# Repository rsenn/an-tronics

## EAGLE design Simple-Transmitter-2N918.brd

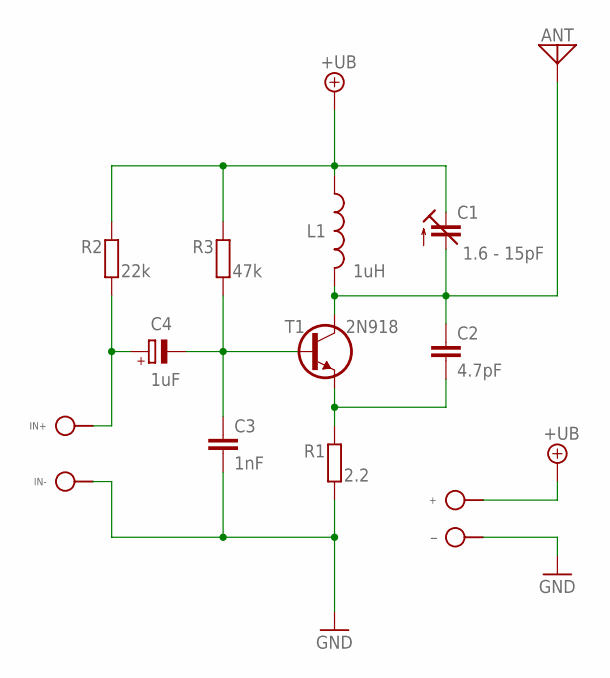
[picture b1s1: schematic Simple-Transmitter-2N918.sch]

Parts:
+: SPAD
ANT: ANT; SPAD
C1: 1.6 - 15pF; TRIM-2222-808
C2: 4.7pF; C025-020X036
C3: 1nF; C025-020X036
C4: 1uF; E2,5-3
IN+: SPAD
IN-: SPAD
L1: 1uH; L-04/7
R1: 2.2; 0202V
R2: 22k; 0202/5
R3: 47k; 0202/5
T1: 2N918; TO-72
̶̶: SPAD

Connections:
+UB: +.1, C1.3 (A), L1.1, R2.2, R3.2
GND: C3.2, IN-.1, R1.1, ̶̶.1
IN+: C4.+, IN+.1, R2.1
unnamed: ANT.1, C1.2 (E), C2.1, L1.2, T1.3 (C)
unnamed: C2.2, R1.2, T1.1 (E), T1.4 (E)
unnamed: C3.1, C4.-, R3.1, T1.2 (B)

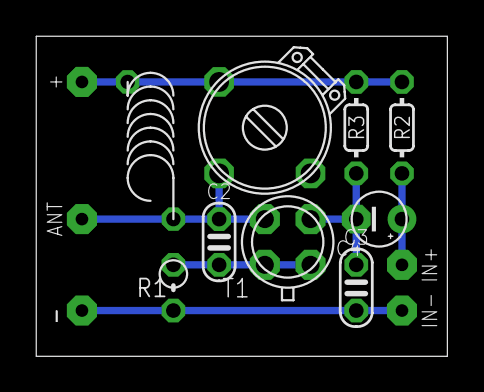
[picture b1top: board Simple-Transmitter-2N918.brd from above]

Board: 2 copper layers, 22.8 x 17.8 mm, 14 parts (0 on the bottom side), 6 nets.

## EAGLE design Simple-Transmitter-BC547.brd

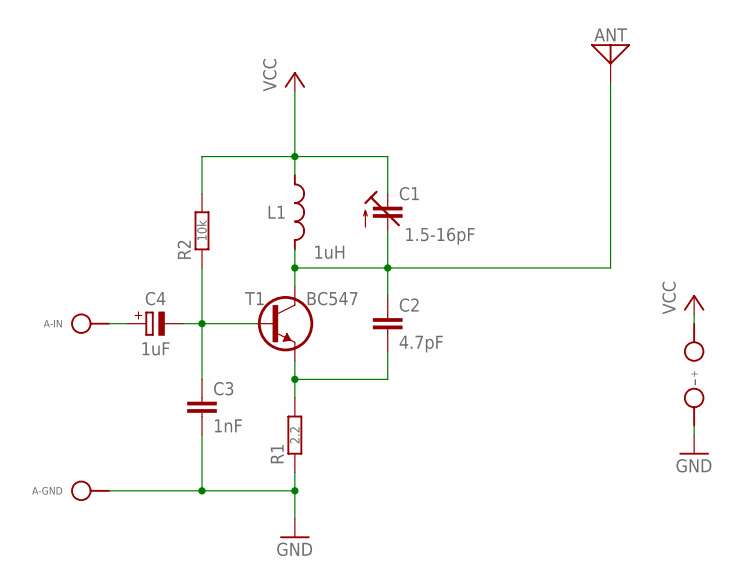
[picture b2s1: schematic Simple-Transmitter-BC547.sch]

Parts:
+: SPAD
A-GND: SPAD
A-IN: SPAD
ANT: ANT; SPAD
C1: 1.5-16pF; TRIM808-45
C2: 4.7pF; C050-020X036-M
C3: 1nF; C050-020X036
C4: 1uF; E2,5-3
L1: 1uH; L-04/7
R1: 2.2; 0202V
R2: 10k; 0202/5-V
T1: BC547; TO92-CBE
̶̶: SPAD

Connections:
AIN: A-IN.1, C4.+
GND: A-GND.1, C3.2, R1.1, ̶̶.1
unnamed: ANT.1, C1.2 (E), C2.1, L1.2, T1.C
unnamed: C2.2, R1.2, T1.E
unnamed: C3.1, C4.-, R2.1, T1.B
VCC: +.1, C1.3 (A), L1.1, R2.2

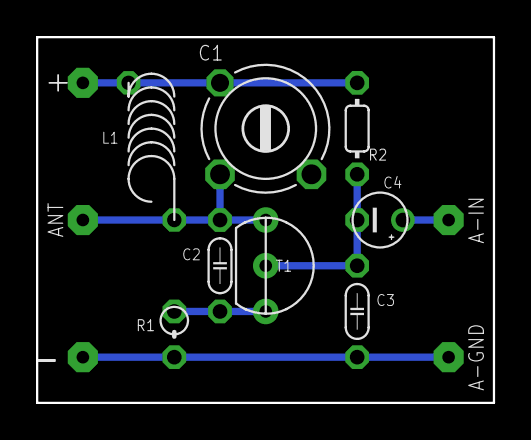
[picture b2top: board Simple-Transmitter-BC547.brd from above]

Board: 2 copper layers, 25.4 x 20.3 mm, 13 parts (0 on the bottom side), 6 nets.

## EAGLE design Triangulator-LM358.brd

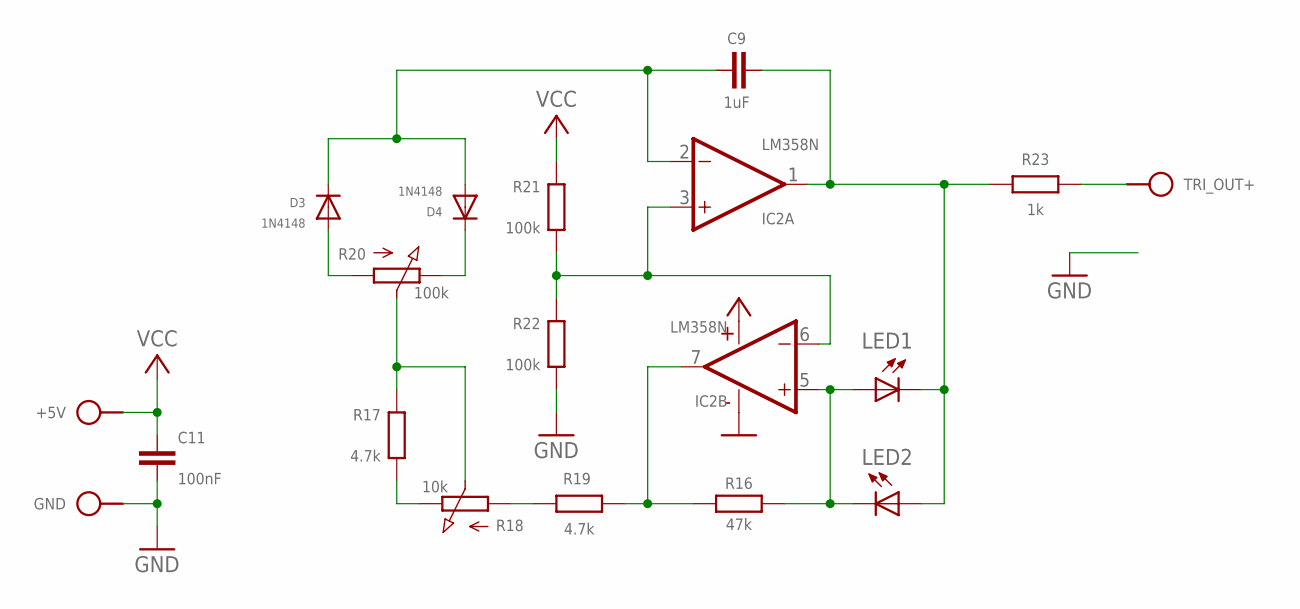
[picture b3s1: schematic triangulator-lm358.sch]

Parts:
+5V: VCC; SPAD
C9: 1uF; C050-020X036/V
C11: 100nF; C050-020X036
D3, D4: 1N4148; DO34-5V
GND: GND; SPAD
IC2: LM358N; DIL08
LED1, LED2: LED3MM
R16: 47k; 0202/7-V
R17: 4.7k; 0202/7
R18: 10k; POT
R19: 4.7k; 0202/7-V
R20: 100k; POT
R21, R22: 100k; 0202/7-V
R23: 1k; 0202/5
TRI_OUT+: TRIANGLE; SPAD

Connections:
GND: C11.2, GND.1, IC2.4 (V-), R22.1
unnamed: IC2.7 (OUT), R16.2, R19.1
unnamed: IC2.5 (+IN), LED1.A, LED2.K (C), R16.1
unnamed: D3.A, R20.1 (A)
unnamed: D4.C, R20.3 (E)
unnamed: R17.2, R18.2 (S), R20.2 (S)
unnamed: R17.1, R18.3 (E)
unnamed: C9.1, D3.C, D4.A, IC2.2 (-IN)
unnamed: R18.1 (A), R19.2
unnamed: C9.2, IC2.1 (OUT), LED1.K (C), LED2.A, R23.2
unnamed: R23.1, TRI_OUT+.1
unnamed: IC2.3 (+IN), IC2.6 (-IN), R21.1, R22.2
VCC: +5V.1, C11.1, IC2.8 (V+), R21.2

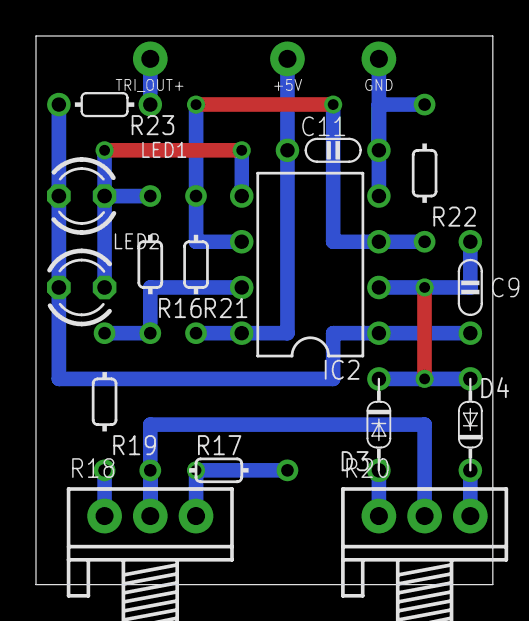
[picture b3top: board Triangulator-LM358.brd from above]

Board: 2 copper layers, 25.4 x 30.5 mm, 18 parts (0 on the bottom side), 13 nets.

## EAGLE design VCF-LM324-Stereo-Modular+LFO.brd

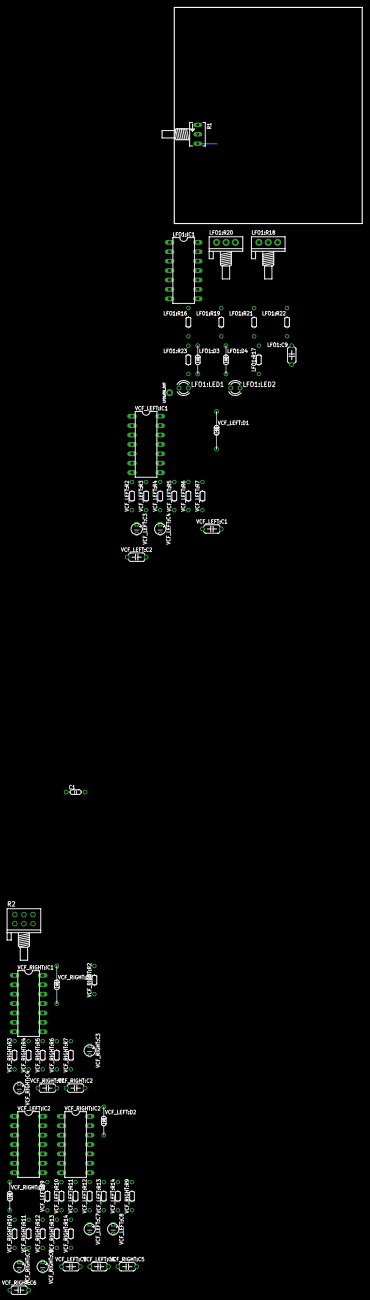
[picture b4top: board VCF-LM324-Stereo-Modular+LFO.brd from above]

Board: 2 copper layers, 50.8 x 58.4 mm, 66 parts (0 on the bottom side), 36 nets.

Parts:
C1: 100nF; C050-020X036
LFO1:C9: 1uF; C050-024X044/V
LFO1:D3, LFO1:D4: 1N4148; DO34-7V
LFO1:IC1: LM324; DIL14
LFO1:LED1, LFO1:LED2: LED3MM
LFO1:R16: 47k; 0202/7-V
LFO1:R17: 4.7k; 0202/7
LFO1:R18: 10k; POT
LFO1:R19: 4.7k; 0202/7-V
LFO1:R20: 100k; POT
LFO1:R21, LFO1:R22: 100k; 0202/7-V
LFO1:R23: 1k; 0202/7-V
LFO1:TRI_OUT: TRIANGLE; SPAD
R1: 100k; B64Y
R2: 10k; POT-STEREO
VCF_LEFT:C1, VCF_LEFT:C2, VCF_LEFT:C5, VCF_LEFT:C6: 100nF; C050-024X044
VCF_LEFT:C3, VCF_LEFT:C4, VCF_LEFT:C7, VCF_LEFT:C8: 1uF; E2,5-3
VCF_LEFT:D1: 1N4148; DO34-10V
VCF_LEFT:D2: 1N4148; DO34-7V
VCF_LEFT:IC1, VCF_LEFT:IC2: LM324; DIL14
VCF_LEFT:R2, VCF_LEFT:R3, VCF_LEFT:R9, VCF_LEFT:R10: 1k; 0202/7
VCF_LEFT:R4, VCF_LEFT:R11: 470k; 0202/7
VCF_LEFT:R5, VCF_LEFT:R6, VCF_LEFT:R7, VCF_LEFT:R12, VCF_LEFT:R13, VCF_LEFT:R14: 100k; 0202/7
VCF_RIGHT:C1, VCF_RIGHT:C2, VCF_RIGHT:C5, VCF_RIGHT:C6: 100nF; C050-024X044
VCF_RIGHT:C3, VCF_RIGHT:C4, VCF_RIGHT:C7, VCF_RIGHT:C8: 1uF; E2,5-3
VCF_RIGHT:D1: 1N4148; DO34-10V
VCF_RIGHT:D2: 1N4148; DO34-7V
VCF_RIGHT:IC1, VCF_RIGHT:IC2: LM324; DIL14
VCF_RIGHT:R2, VCF_RIGHT:R3, VCF_RIGHT:R9, VCF_RIGHT:R10: 1k; 0202/7
VCF_RIGHT:R4, VCF_RIGHT:R11: 470k; 0202/7
VCF_RIGHT:R5, VCF_RIGHT:R6, VCF_RIGHT:R7, VCF_RIGHT:R12, VCF_RIGHT:R13, VCF_RIGHT:R14: 100k; 0202/7

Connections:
CV_POT: R1.S, VCF_LEFT:R2.2, VCF_RIGHT:R2.2
GND: C1.2, LFO1:R22.1, R1.A, VCF_LEFT:D1.C, VCF_LEFT:D2.C, VCF_LEFT:IC1.11, VCF_LEFT:R6.1, VCF_LEFT:R13.1, VCF_RIGHT:D1.C, VCF_RIGHT:D2.C, VCF_RIGHT:IC1.11, VCF_RIGHT:R6.1, VCF_RIGHT:R13.1
LFO1:N$14: LFO1:IC1.7, LFO1:R16.2, LFO1:R19.1
LFO1:N$15: LFO1:IC1.5, LFO1:LED1.A, LFO1:LED2.K, LFO1:R16.1
LFO1:N$26: LFO1:C9.1, LFO1:D3.C, LFO1:D4.A, LFO1:IC1.9
LFO1:N$28: LFO1:C9.2, LFO1:IC1.8, LFO1:LED1.K, LFO1:LED2.A, LFO1:R23.2
LFO1:OA_C_IN+: LFO1:IC1.6, LFO1:IC1.10, LFO1:R21.1, LFO1:R22.2
LFO1:TRIM_1_A: LFO1:D3.A, LFO1:R20.1
LFO1:TRIM_1_B: LFO1:D4.C, LFO1:R20.3
LFO1:TRIM_2_A: LFO1:R17.1, LFO1:R18.3
LFO1:TRIM_2_B: LFO1:R18.1, LFO1:R19.2
LFO1:TRIM_P: LFO1:R17.2, LFO1:R18.2, LFO1:R20.2
unnamed: R2.1-2, R2.1-3, VCF_LEFT:C3.+, VCF_LEFT:IC1.1, VCF_LEFT:R7.2
unnamed: R2.1-1, VCF_LEFT:C2.2
unnamed: R2.2-2, R2.2-3, VCF_RIGHT:C3.+, VCF_RIGHT:IC1.1, VCF_RIGHT:R7.2
unnamed: R2.2-1, VCF_RIGHT:C2.2
unnamed: LFO1:R23.1, LFO1:TRI_OUT.1, VCF_LEFT:R3.2, VCF_RIGHT:R3.2
VCC: C1.1, LFO1:R21.2, R1.E, VCF_LEFT:IC1.4, VCF_LEFT:R5.1, VCF_LEFT:R12.1, VCF_RIGHT:IC1.4, VCF_RIGHT:R5.1, VCF_RIGHT:R12.1
VCF_LEFT:N$2: VCF_LEFT:C1.1, VCF_LEFT:IC1.2, VCF_LEFT:R4.2, VCF_LEFT:R7.1
VCF_LEFT:N$7: VCF_LEFT:IC1.3, VCF_LEFT:R5.2, VCF_LEFT:R6.2
VCF_LEFT:N$9: VCF_LEFT:C1.2, VCF_LEFT:C2.1, VCF_LEFT:D1.A, VCF_LEFT:R2.1, VCF_LEFT:R3.1
VCF_LEFT:N$10: VCF_LEFT:C4.-, VCF_LEFT:R4.1
VCF_LEFT:N$13: VCF_LEFT:IC2.13, VCF_LEFT:R12.2, VCF_LEFT:R13.2
VCF_LEFT:N$16: VCF_LEFT:C5.2, VCF_LEFT:C6.1, VCF_LEFT:D2.A, VCF_LEFT:R9.1, VCF_LEFT:R10.1
VCF_LEFT:N$17: VCF_LEFT:C5.1, VCF_LEFT:IC2.12, VCF_LEFT:R11.2, VCF_LEFT:R14.1
VCF_LEFT:N$20: VCF_LEFT:C8.-, VCF_LEFT:R11.1
VCF_LEFT:R_P_R_IN: VCF_LEFT:C7.+, VCF_LEFT:IC2.14, VCF_LEFT:R14.2
VCF_RIGHT:N$2: VCF_RIGHT:C1.1, VCF_RIGHT:IC1.2, VCF_RIGHT:R4.2, VCF_RIGHT:R7.1
VCF_RIGHT:N$7: VCF_RIGHT:IC1.3, VCF_RIGHT:R5.2, VCF_RIGHT:R6.2
VCF_RIGHT:N$9: VCF_RIGHT:C1.2, VCF_RIGHT:C2.1, VCF_RIGHT:D1.A, VCF_RIGHT:R2.1, VCF_RIGHT:R3.1
VCF_RIGHT:N$10: VCF_RIGHT:C4.-, VCF_RIGHT:R4.1
VCF_RIGHT:N$13: VCF_RIGHT:IC2.13, VCF_RIGHT:R12.2, VCF_RIGHT:R13.2
VCF_RIGHT:N$16: VCF_RIGHT:C5.2, VCF_RIGHT:C6.1, VCF_RIGHT:D2.A, VCF_RIGHT:R9.1, VCF_RIGHT:R10.1
VCF_RIGHT:N$17: VCF_RIGHT:C5.1, VCF_RIGHT:IC2.12, VCF_RIGHT:R11.2, VCF_RIGHT:R14.1
VCF_RIGHT:N$20: VCF_RIGHT:C8.-, VCF_RIGHT:R11.1
VCF_RIGHT:R_P_R_IN: VCF_RIGHT:C7.+, VCF_RIGHT:IC2.14, VCF_RIGHT:R14.2

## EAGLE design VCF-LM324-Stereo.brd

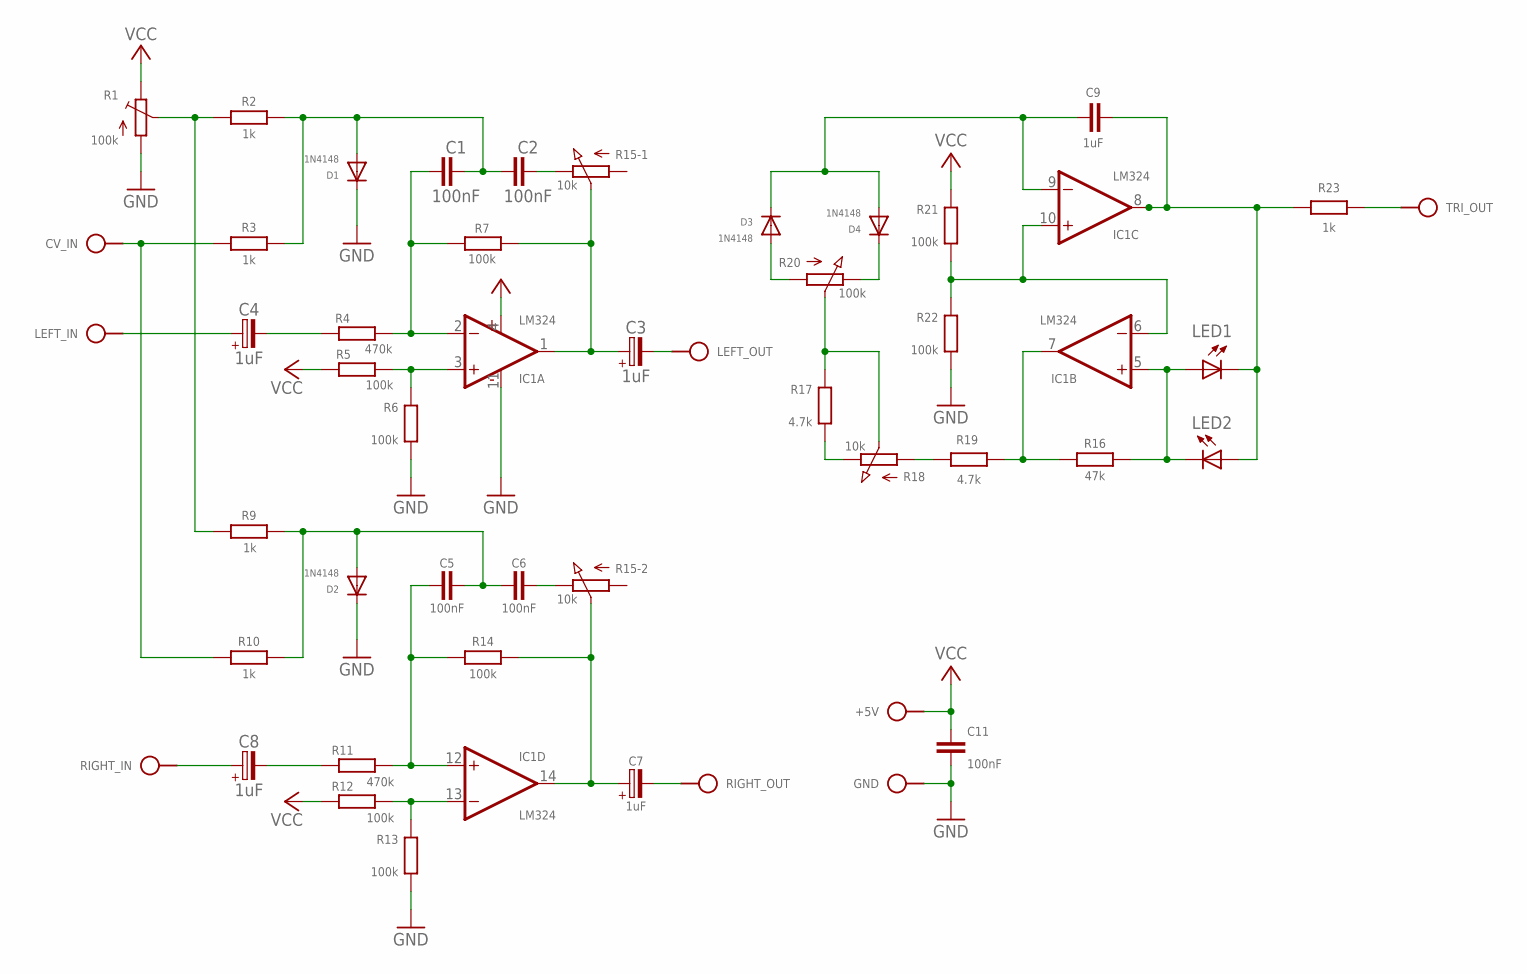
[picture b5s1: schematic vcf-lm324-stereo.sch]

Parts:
+5V: VCC; SPAD
C1, C2, C5, C6: 100nF; C050-024X044
C3, C4, C7, C8: 1uF; E2,5-3
C9: 1uF; C050-024X044/V
C11: 100nF; C050-020X036
CV_IN: CV_IN; SPAD
D1: 1N4148; DO34-10V
D2, D3, D4: 1N4148; DO34-7V
GND: GND; SPAD
IC1: LM324; DIL14
LED1, LED2: LED3MM
LEFT_IN: AUDIO_IN; SPAD
LEFT_OUT: AUDIO_OUT; SPAD
R1: 100k; B64Y
R2, R3, R9, R10: 1k; 0202/7
R4, R11: 470k; 0202/7
R5, R6, R7, R12, R13, R14: 100k; 0202/7
R15: 10k; POT-STEREO
R16: 47k; 0202/7-V
R17: 4.7k; 0202/7
R18: 10k; POT
R19: 4.7k; 0202/7-V
R20: 100k; POT
R21, R22: 100k; 0202/7-V
R23: 1k; 0202/7-V
RIGHT_IN: AUDIO_IN; SPAD
RIGHT_OUT: AUDIO_OUT; SPAD
TRI_OUT: TRIANGLE; SPAD

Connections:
GND: C11.2, D1.C, D2.C, GND.1, IC1.11 (V-), R1.A, R6.1, R13.1, R22.1
unnamed: C4.+, LEFT_IN.1
unnamed: C1.1, IC1.2 (-IN), R4.2, R7.1
unnamed: C2.2, R15.1-3 (E)
unnamed: C3.+, IC1.1 (OUT), R7.2, R15.1-2 (S)
unnamed: R1.S, R2.2, R9.2
unnamed: C3.-, LEFT_OUT.1
unnamed: IC1.3 (+IN), R5.2, R6.2
unnamed: CV_IN.1, R3.2, R10.2
unnamed: C1.2, C2.1, D1.A, R2.1, R3.1
unnamed: C4.-, R4.1
unnamed: C6.2, R15.2-3 (E)
unnamed: C7.+, IC1.14 (OUT), R14.2, R15.2-2 (S)
unnamed: IC1.13 (-IN), R12.2, R13.2
unnamed: IC1.7 (OUT), R16.2, R19.1
unnamed: IC1.5 (+IN), LED1.A, LED2.K (C), R16.1
unnamed: C5.2, C6.1, D2.A, R9.1, R10.1
unnamed: C5.1, IC1.12 (+IN), R11.2, R14.1
unnamed: C7.-, RIGHT_OUT.1
unnamed: C8.+, RIGHT_IN.1
unnamed: C8.-, R11.1
unnamed: C9.1, D3.C, D4.A, IC1.9 (-IN)
unnamed: C9.2, IC1.8 (OUT), LED1.K (C), LED2.A, R23.2
OA_C_IN+: IC1.6 (-IN), IC1.10 (+IN), R21.1, R22.2
TRIM_1_A: D3.A, R20.1 (A)
TRIM_1_B: D4.C, R20.3 (E)
TRIM_2_A: R17.1, R18.3 (E)
TRIM_2_B: R18.1 (A), R19.2
TRIM_P: R17.2, R18.2 (S), R20.2 (S)
TRI_OUT: R23.1, TRI_OUT.1
VCC: +5V.1, C11.1, IC1.4 (V+), R1.E, R5.1, R12.1, R21.2

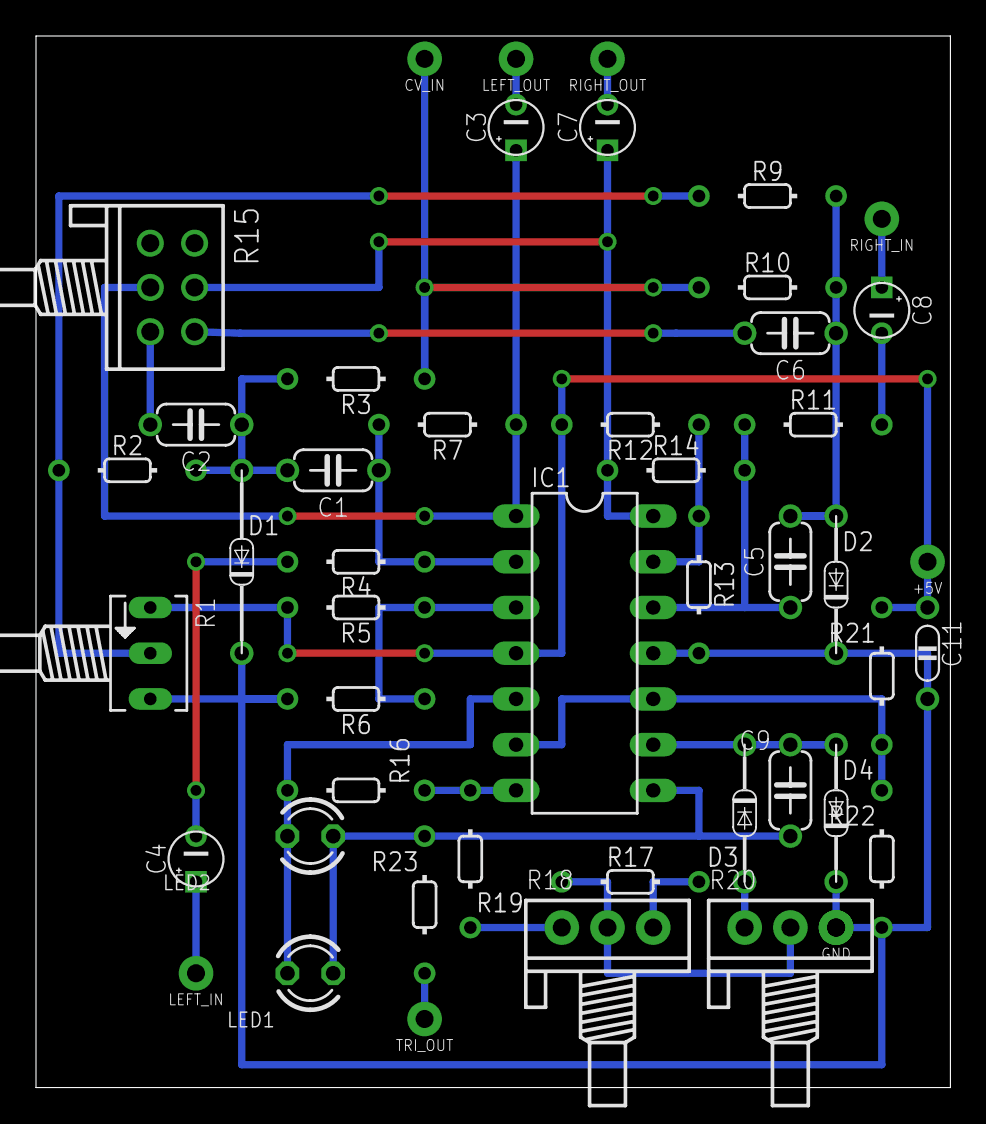
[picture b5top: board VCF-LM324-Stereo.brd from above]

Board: 2 copper layers, 50.8 x 58.4 mm, 47 parts (0 on the bottom side), 31 nets.

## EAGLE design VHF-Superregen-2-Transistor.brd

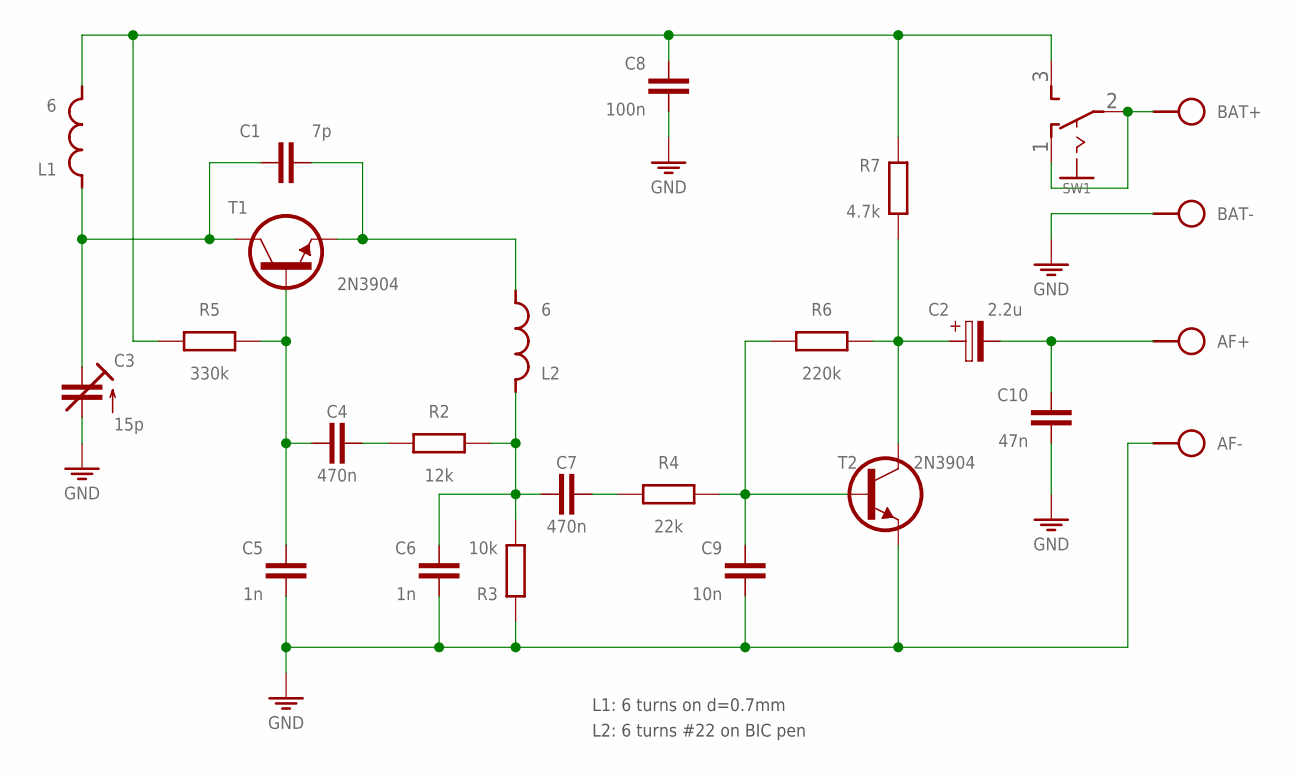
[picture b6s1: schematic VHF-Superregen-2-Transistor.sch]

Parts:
AF+: SPAD
AF-: SPAD
BAT+: SPAD
BAT-: SPAD
C1: 7p; C050-020X036
C2: 2.2u; E2,5-3
C3: 15p; TRIM-2222-808
C4: 470n; C050-020X036
C5, C6: 1n; C025-020X036
C7: 470n; C050-020X044
C8: 100n; C050-020X044/V
C9: 10n; C050-020X036/V
C10: 47n; C050-020X036
L1: 6; L-02/7V
L2: 6; L-02/5V
R2: 12k; 0202/7
R3: 10k; 0202/7
R4: 22k; 0202/7
R5: 330k; 0202/7-V
R6: 220k; 0202/7
R7: 4.7k; 0202/7-V
SW1: SL-SW-1P-2T-H; SLSW-1P2T-H
T1, T2: 2N3904; TO92

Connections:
GND: AF-.1, BAT-.1, C3.2 (A), C5.2, C6.2, C8.2, C9.2, C10.2, R3.2, T2.1 (E)
unnamed: C1.2, C3.1 (E), L1.1, T1.3 (C)
unnamed: C1.1, L2.2, T1.1 (E)
unnamed: C4.2, C5.1, R5.2, T1.2 (B)
unnamed: C2.+, R6.2, R7.1, T2.3 (C)
unnamed: C6.1, C7.2, L2.1, R2.2, R3.1
unnamed: C4.1, R2.1
unnamed: C7.1, R4.1
unnamed: BAT+.1, SW1.1 (O), SW1.2
unnamed: C9.1, R4.2, R6.1, T2.2 (B)
unnamed: AF+.1, C2.-, C10.1
VCC: C8.1, L1.2, R5.1, R7.2, SW1.3 (S)

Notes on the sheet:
L1: 6 turns on d=0.7mm
L2: 6 turns #22 on BIC pen

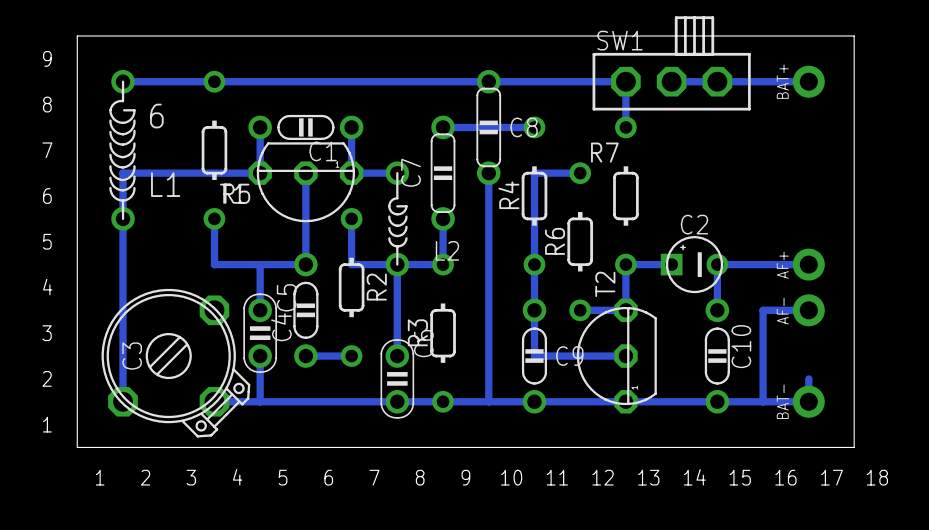
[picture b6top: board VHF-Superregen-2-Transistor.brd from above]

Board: 2 copper layers, 43.2 x 22.9 mm, 25 parts (0 on the bottom side), 12 nets.

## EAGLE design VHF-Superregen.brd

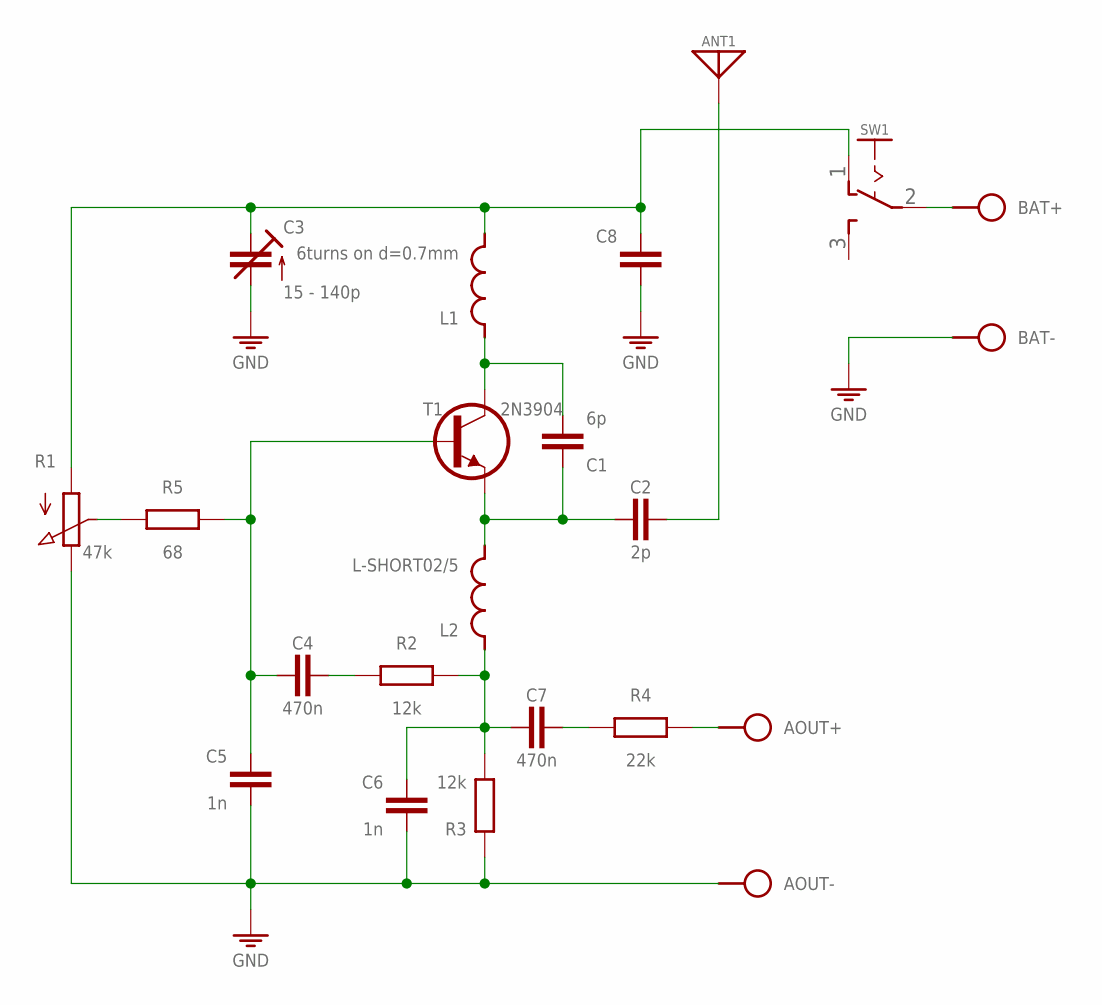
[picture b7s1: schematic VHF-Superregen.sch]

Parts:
ANT1: ANT; SPAD
AOUT+: SPAD
AOUT-: SPAD
BAT+: SPAD
BAT-: SPAD
C1: 6p; C050-020X036
C2: 2p; C025-015X024
C3: 15 - 140p; TRIM-2222-808
C4, C7: 470n; C025-015X024
C5, C6: 1n; C025-020X036
C8: C050-025X075
L1: 6turns on d=0.7mm; L-04/7V
L2: L-SHORT02/5; L-02/5V
R1: 47k; POT
R2, R3: 12k; 0202/7
R4: 22k; 0202/7
R5: 68; 0202/7
SW1: SL-SW-1P-2T-H; SLSW-1P2T-H
T1: 2N3904; TO92

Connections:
GND: AOUT-.1, BAT-.1, C3.2 (A), C5.2, C6.2, C8.2, R1.3 (E), R3.2
unnamed: C1.2, L1.1, T1.3 (C)
unnamed: C1.1, C2.2, L2.2, T1.1 (E)
unnamed: C3.3 (E), C8.1, L1.2, R1.1 (A), SW1.1 (O)
unnamed: C4.2, C5.1, R5.2, T1.2 (B)
unnamed: ANT1.1, C2.1
unnamed: C4.1, R2.1
unnamed: C7.1, R4.1
unnamed: BAT+.1, SW1.2
unnamed: AOUT+.1, R4.2
unnamed: R1.2 (S), R5.1
unnamed: C6.1, C7.2, L2.1, R2.2, R3.1

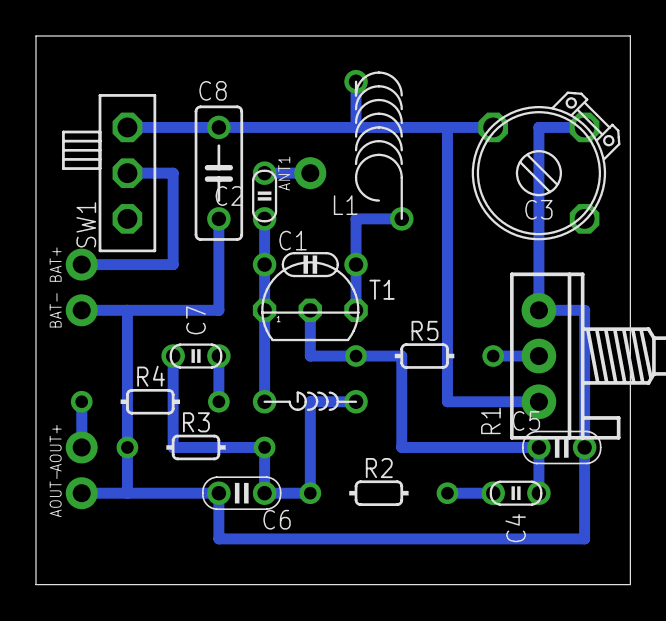
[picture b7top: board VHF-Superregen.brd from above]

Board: 2 copper layers, 33.0 x 30.5 mm, 22 parts (0 on the bottom side), 12 nets.

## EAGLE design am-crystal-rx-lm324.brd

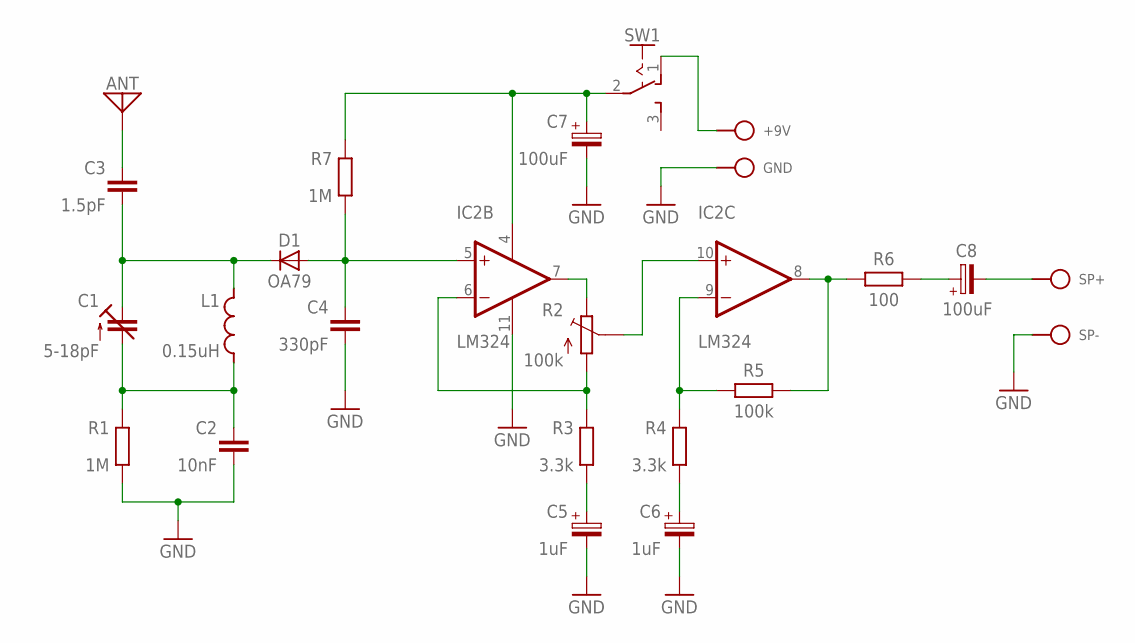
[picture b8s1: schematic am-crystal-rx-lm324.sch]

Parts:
+9V: BAT+; SPAD
ANT: ANT; SPAD
C1: 5-18pF; TRIM-2222-808
C2: 10nF; C050-025X075/V
C3: 1.5pF; C050-020X036
C4: 330pF; C050-024X044/V
C5: 1uF; E2.5-4/V
C6: 1uF; E2,5-3
C7: 100uF; E5-5/V
C8: 100uF; E2,5-5/V
D1: OA79; OA79-18/V
GND: BAT-; SPAD
IC2: LM324; DIL14
L1: 0.15uH; L-04-5/5
R1, R7: 1M; 0202/7-V
R2: 100k; B64Y
R3: 3.3k; 0202/7
R4: 3.3k; 0202/7-V
R5: 100k; 0202/7-V
R6: 100; 0202/7-V
SP+: SPKR+; SPAD
SP-: SPKR-; SPAD
SW1: SL-SW-1P-2T-H; SLSW-1P2T-H

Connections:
A: IC2.7 (OUT), R2.E
E: IC2.6 (-IN), R2.A, R3.2
GND: C2.2, C4.2, C5.-, C6.-, C7.-, GND.1, IC2.11 (V-), R1.1, SP-.1
unnamed: C4.1, D1.A, IC2.5 (+IN), R7.1
unnamed: C7.+, IC2.4 (V+), R7.2, SW1.2
unnamed: C1.1 (A), C2.1, L1.1, R1.2
unnamed: C1.2 (E), C3.2, D1.C, L1.2
unnamed: ANT.1, C3.1
unnamed: IC2.8 (OUT), R5.1, R6.2
unnamed: IC2.9 (-IN), R4.2, R5.2
unnamed: C5.+, R3.1
unnamed: C6.+, R4.1
unnamed: C8.+, R6.1
unnamed: C8.-, SP+.1
unnamed: +9V.1, SW1.1 (O)
S: IC2.10 (+IN), R2.S

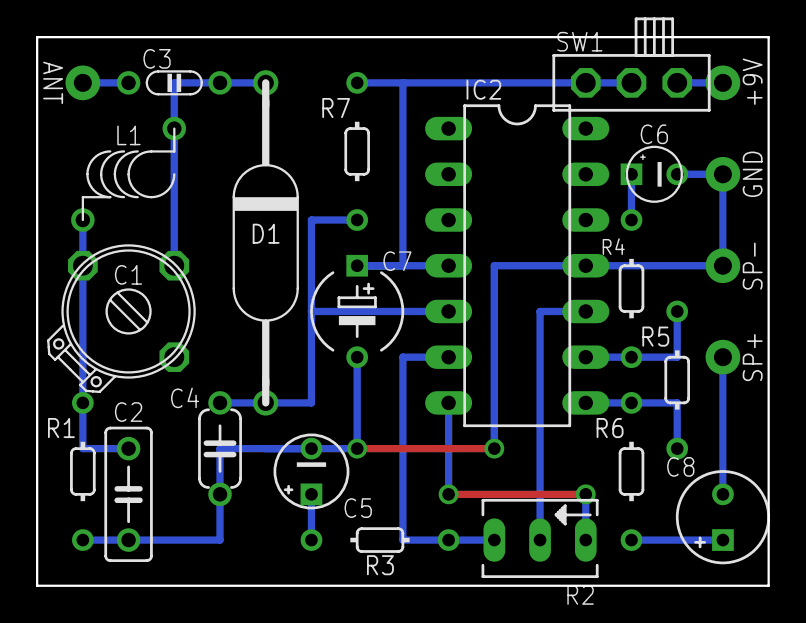
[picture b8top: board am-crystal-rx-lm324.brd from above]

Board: 2 copper layers, 40.6 x 30.5 mm, 24 parts (0 on the bottom side), 16 nets.
